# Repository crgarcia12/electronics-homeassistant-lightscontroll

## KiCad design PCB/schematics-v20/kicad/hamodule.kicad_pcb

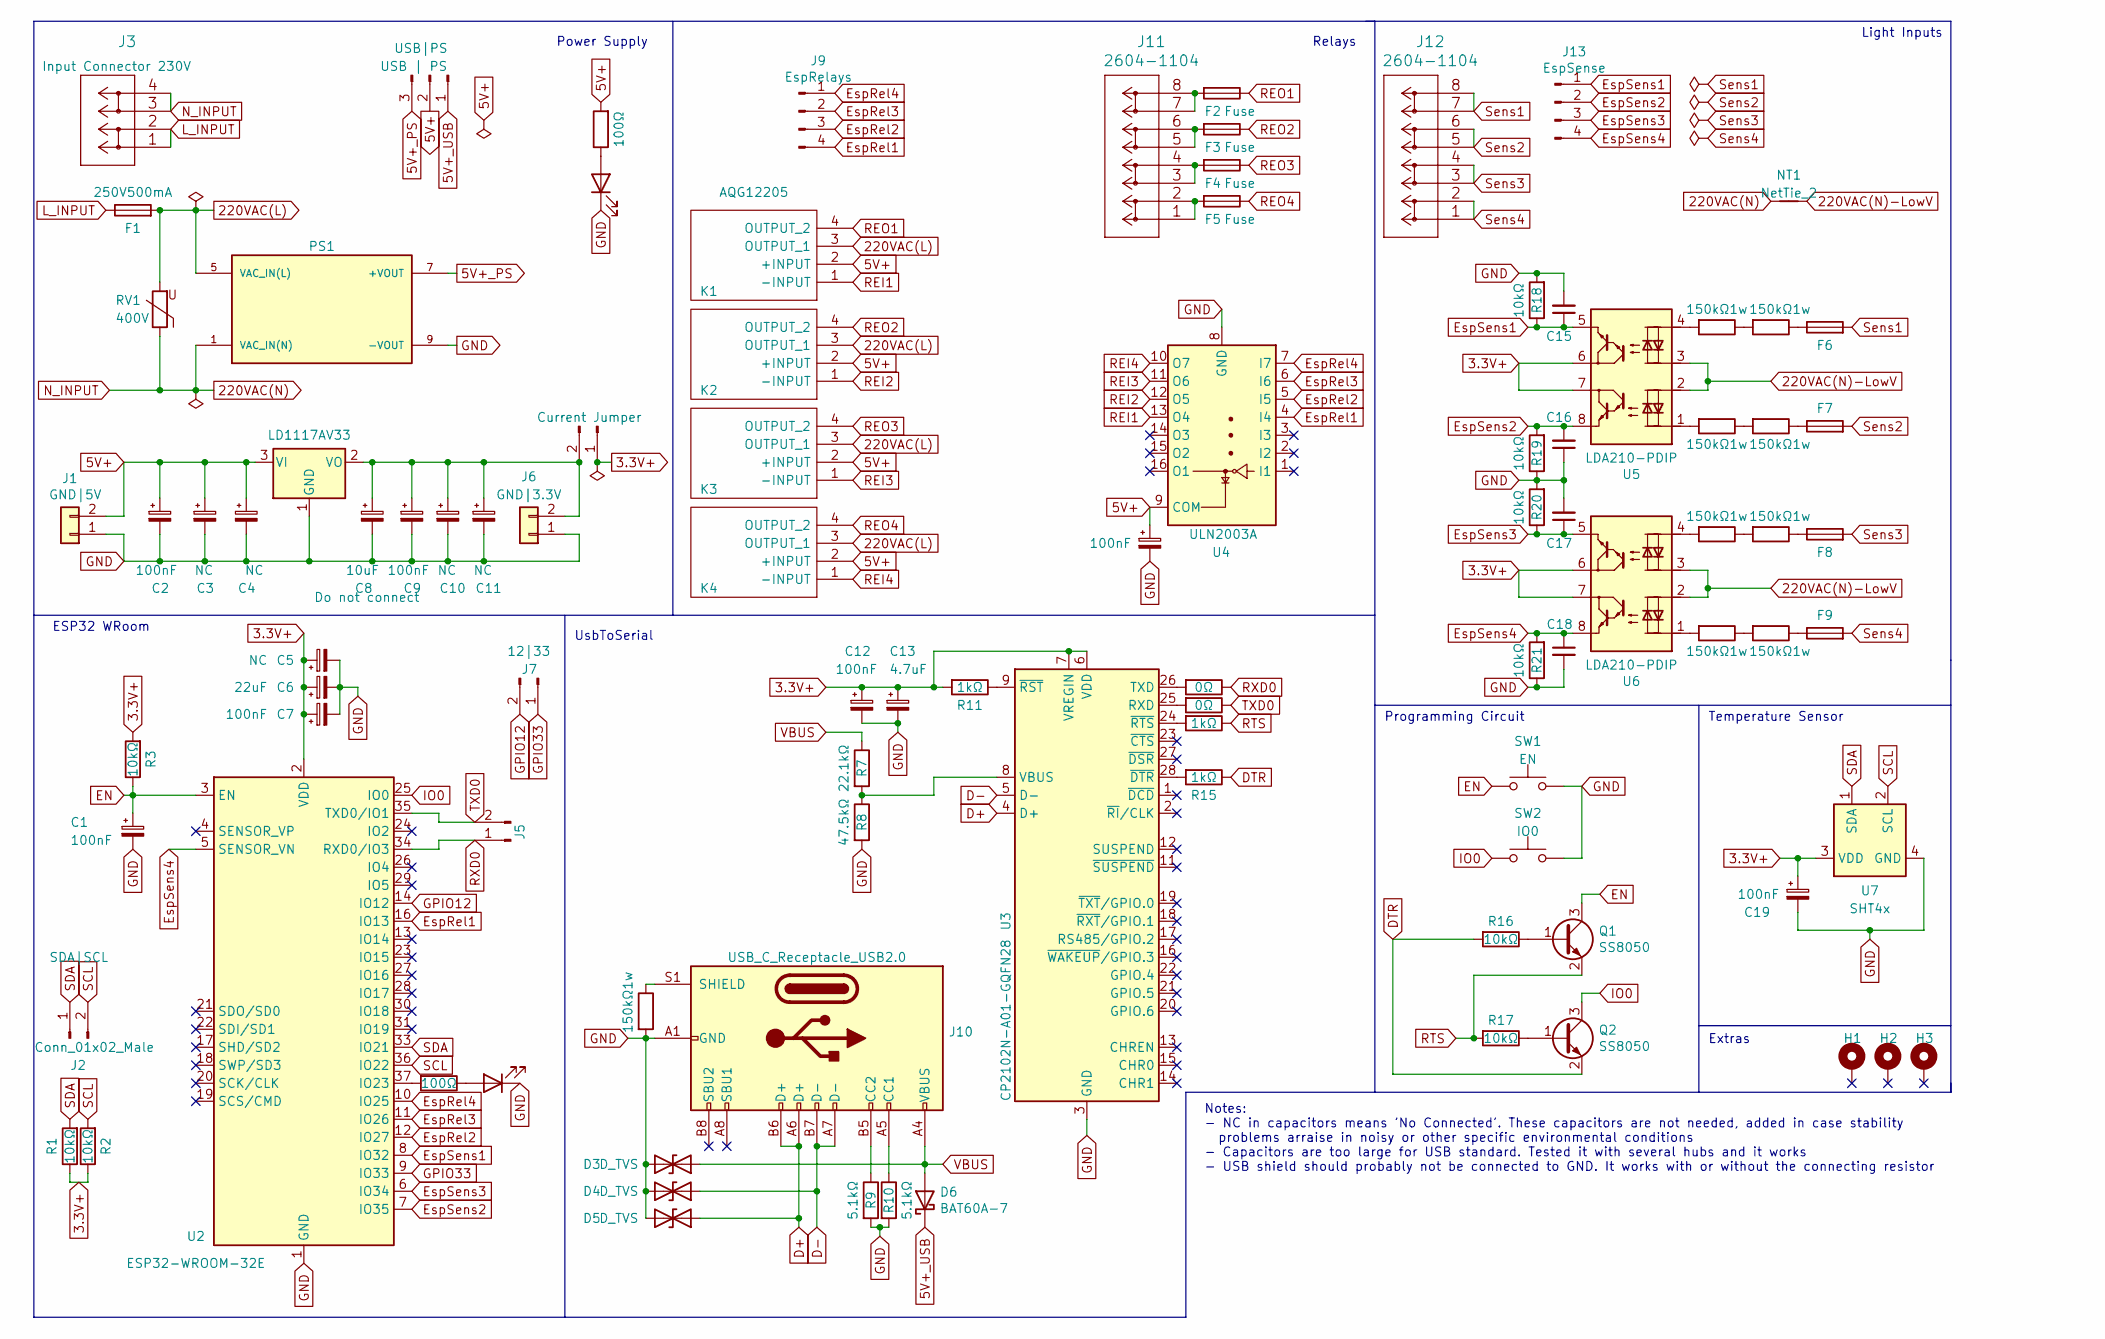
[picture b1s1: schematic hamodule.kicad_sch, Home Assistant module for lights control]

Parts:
C1, C2, C7, C9, C12, C14, C19: 100nF; C_0603_1608Metric_Pad1.08x0.95mm_HandSolder; JLCPCB C14663
C3, C4, C10, C11: NC; C_0805_2012Metric_Pad1.18x1.45mm_HandSolder
C5: NC; C_0603_1608Metric_Pad1.08x0.95mm_HandSolder
C6, C15, C16, C17, C18: 22uF; C_0603_1608Metric_Pad1.08x0.95mm_HandSolder; JLCPCB C59461
C8: 10uF; CP_Radial_D6.3mm_P2.50mm
C13: 4.7uF; C_0603_1608Metric_Pad1.08x0.95mm_HandSolder; JLCPCB C19666
D1, D2: LED; LED_0805_2012Metric_Pad1.15x1.40mm_HandSolder; JLCPCB C2297
D3, D4, D5: D_TVS; D_SOD-523; JLCPCB C383211
D6: BAT60A-7; D_SOD-323; JLCPCB C124187
F1: 250V500mA; Fuseholder_TR5_Littelfuse_No560_No460
F2, F3, F4, F5, F6, F7, F8, F9: Fuse; FUSE_RST-1-BULK
H1, H2, H3: MountingHole_Pad; MountingHole_3.2mm_M3_ISO14580_Pad
J1: GND|5V; JST_XH_B2B-XH-A_1x02_P2.50mm_Vertical
J2, J5, J7: Conn_01x02_Male; PinHeader_1x02_P2.54mm_Vertical
J3: 2604-1102; big_pads_2604-1102
J4: USB | PS; PinHeader_1x03_P2.54mm_Vertical
J6: GND|3.3V; JST_XH_B2B-XH-A_1x02_P2.50mm_Vertical
J8: Current Jumper; PinHeader_1x02_P2.54mm_Vertical
J9: EspRelays; PinSocket_1x04_P2.54mm_Vertical
J10: USB_C_Receptacle_USB2.0; USB_C_Receptacle_HRO_TYPE-C-31-M-12; JLCPCB C167321
J11, J12: 2604-1104; big_pads_2604-1104
J13: EspSense; PinSocket_1x04_P2.54mm_Vertical
K1, K2, K3, K4: AQG12205; Manufacturer_Part_Number AQG12205; Mouser Part Number 769-AQG12205
NT1: NetTie_2; NetTie-2_SMD_Pad2.0mm
PS1: RAC05-05SK/277; 277; PARTREV N/A
Q1, Q2: SS8050; SOT-23; JLCPCB C177739
R1, R2, R3, R16, R17, R18, R19, R20, R21: 10kΩ; R_0603_1608Metric_Pad0.98x0.95mm_HandSolder; JLCPCB C25804
R4, R5: 100Ω; R_0805_2012Metric_Pad1.20x1.40mm_HandSolder; JLCPCB C17408
R6, R22, R23, R24, R25, R26, R27, R28, R29: 150kΩ1w; R_2512_6332Metric_Pad1.40x3.35mm_HandSolder; JLCPCB C25719
R7: 22.1kΩ; R_0603_1608Metric_Pad0.98x0.95mm_HandSolder; JLCPCB C25961
R8: 47.5kΩ; R_0603_1608Metric_Pad0.98x0.95mm_HandSolder; JLCPCB C23061
R9, R10: 5.1kΩ; R_0603_1608Metric_Pad0.98x0.95mm_HandSolder; JLCPCB C23186
R11, R15: 1kΩ; R_0603_1608Metric_Pad0.98x0.95mm_HandSolder; JLCPCB C25585
R12, R13: 0Ω; R_0805_2012Metric_Pad1.20x1.40mm_HandSolder; JLCPCB C17477
R14: 1kΩ; R_1206_3216Metric_Pad1.30x1.75mm_HandSolder; JLCPCB C4410
RV1: 400V; RV_Disc_D12mm_W4.2mm_P7.5mm
SW1, SW2: Switch; SW_SPST_SKQG_WithStem; JLCPCB C318884
U1: LD1117AV33; TO-220-3_Vertical
U2: ESP32-WROOM-32E; ESP32-WROOM-32; JLCPCB C701343
U3: CP2102N-A01-GQFN28; QFN-28-1EP_5x5mm_P0.5mm_EP3.35x3.35mm; JLCPCB C964632
U4: ULN2003A; SOIC-16_3.9x9.9mm_P1.27mm; JLCPCB C7512
U5, U6: LDA210-PDIP; DIP-8_W7.62mm_Socket_LongPads
U7: SHT4x; XDCR_SHT40-AD1B-R2; JLCPCB C2909890

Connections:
3.3V+: C5.1, C6.1, C7.1, C12.1, C13.1, C19.1, J8.1, R1.1, R2.1, R3.2, R11.2, U2.2 (VDD), U3.6 (VDD), U3.7 (VREGIN), U5.6, U5.7, U6.6, U6.7, U7.3 (VDD)
5V+: C2.1, C3.1, C4.1, C14.1, J1.2, J4.2, K1.2 (+INPUT), K2.2 (+INPUT), K3.2 (+INPUT), K4.2 (+INPUT), R5.2, U1.3 (VI), U4.9 (COM)
5V+_PS: J4.3, PS1.7 (+VOUT)
5V+_USB: D6.1 (K), J4.1
220VAC(L): F1.2, K1.3 (OUTPUT_1), K2.3 (OUTPUT_1), K3.3 (OUTPUT_1), K4.3 (OUTPUT_1), PS1.5 (VAC_IN(L)), RV1.2
220VAC(N): J3.3, J3.4, NT1.1, PS1.1 (VAC_IN(N)), RV1.1
220VAC(N)-LowV: NT1.2, U5.2, U5.3, U6.2, U6.3
D+: D5.1 (A1), J10.A6 (D+), J10.B6 (D+), U3.4 (D+)
D-: D4.1 (A1), J10.A7 (D-), J10.B7 (D-), U3.5 (D-)
DTR: Q2.2 (E), R15.1, R16.2
EN: C1.1, Q1.3 (C), R3.1, SW1.1, U2.3 (EN)
EspRel1: J9.4, U2.16 (IO13), U4.4 (I4)
EspRel2: J9.3, U2.12 (IO27), U4.5 (I5)
EspRel3: J9.2, U2.11 (IO26), U4.6 (I6)
EspRel4: J9.1, U2.10 (IO25), U4.7 (I7)
EspSens1: C15.1, J13.1, R18.1, U2.8 (IO32), U5.5
EspSens2: C16.2, J13.2, R19.2, U2.7 (IO35), U5.8
EspSens3: C17.1, J13.3, R20.1, U2.6 (IO34), U6.5
EspSens4: C18.1, J13.4, R21.2, U2.5 (SENSOR_VN), U6.8
GND: C1.2, C2.2, C3.2, C4.2, C5.2, C6.2, C7.2, C8.2, C9.2, C10.2, C11.2, C12.2, C13.2, C14.2, C15.2, C16.1, C17.2, C18.2, C19.2, D1.1 (K), D2.1 (K), D3.2 (A2), D4.2 (A2), D5.2 (A2), J1.1, J6.1, J10.A1 (GND), J10.A12 (GND), J10.B1 (GND), J10.B12 (GND), PS1.9 (-VOUT), R6.2, R8.2, R9.2, R10.2, R18.2, R19.1, R20.2, R21.1, SW1.2, SW2.2, U1.1 (GND), U2.1 (GND), U2.15 (GND), U2.38 (GND), U2.39 (GND), U3.3 (GND), U3.29 (GND), U4.8 (GND), U7.4 (GND)
GPIO12: J7.2, U2.14 (IO12)
GPIO33: J7.1, U2.9 (IO33)
IO0: Q2.3 (C), SW2.1, U2.25 (IO0)
L_INPUT: F1.1, J3.1, J3.2
unnamed: C8.1, C9.1, C10.1, C11.1, J6.2, J8.2, U1.2 (VO)
unnamed: D1.2 (A), R4.1
unnamed: D2.2 (A), R5.1
unnamed: F6.1, R26.1
unnamed: F7.1, R27.1
unnamed: F8.1, R28.1
unnamed: F9.1, R29.1
unnamed: J10.A5 (CC1), R10.1
unnamed: J10.B5 (CC2), R9.1
unnamed: J10.S1 (SHIELD), R6.1
unnamed: F5.2, J11.1, J11.2
unnamed: F4.2, J11.3, J11.4
unnamed: F3.2, J11.5, J11.6
unnamed: F2.2, J11.7, J11.8
unnamed: Q1.1 (B), R16.1
unnamed: Q2.1 (B), R17.1
unnamed: R4.2, U2.37 (IO23)
unnamed: R7.2, R8.1, U3.8 (VBUS)
unnamed: R11.1, U3.9 (~RST)
unnamed: R12.2, U3.26 (TXD)
unnamed: R13.2, U3.25 (RXD)
unnamed: R14.2, U3.24 (~RTS)
unnamed: R15.2, U3.28 (~DTR)
unnamed: R22.1, R26.2
unnamed: R22.2, U5.4
unnamed: R23.1, R27.2
unnamed: R23.2, U5.1
unnamed: R24.1, R28.2
unnamed: R24.2, U6.4
unnamed: R25.1, R29.2
unnamed: R25.2, U6.1
REI1: K1.1 (-INPUT), U4.13 (O4)
REI2: K2.1 (-INPUT), U4.12 (O5)
REI3: K3.1 (-INPUT), U4.11 (O6)
REI4: K4.1 (-INPUT), U4.10 (O7)
REO1: F2.1, K1.4 (OUTPUT_2)
REO2: F3.1, K2.4 (OUTPUT_2)
REO3: F4.1, K3.4 (OUTPUT_2)
REO4: F5.1, K4.4 (OUTPUT_2)
RTS: Q1.2 (E), R14.1, R17.2
RXD0: J5.1, R12.1, U2.34 (RXD0/IO3)
SCL: J2.2, R2.2, U2.36 (IO22), U7.2 (SCL)
SDA: J2.1, R1.2, U2.33 (IO21), U7.1 (SDA)
Sens1: F6.2, J12.7, J12.8
Sens2: F7.2, J12.5, J12.6
Sens3: F8.2, J12.3, J12.4
Sens4: F9.2, J12.1, J12.2
TXD0: J5.2, R13.1, U2.35 (TXD0/IO1)
VBUS: D3.1 (A1), D6.2 (A), J10.A4 (VBUS), J10.A9 (VBUS), J10.B4 (VBUS), J10.B9 (VBUS), R7.1

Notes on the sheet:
Programming Circuit
UsbToSerial
Relays
Temperature Sensor
Power Supply
Extras
ESP32 WRoom
Notes: - NC in capacitors means 'No Connected'. These capacitors are not needed, added in case stability problems arraise in noisy or other specific environmental conditions - Capacitors are too large for USB standard. Tested it with several hubs and it works - USB shield should probably not be con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
Light Inputs

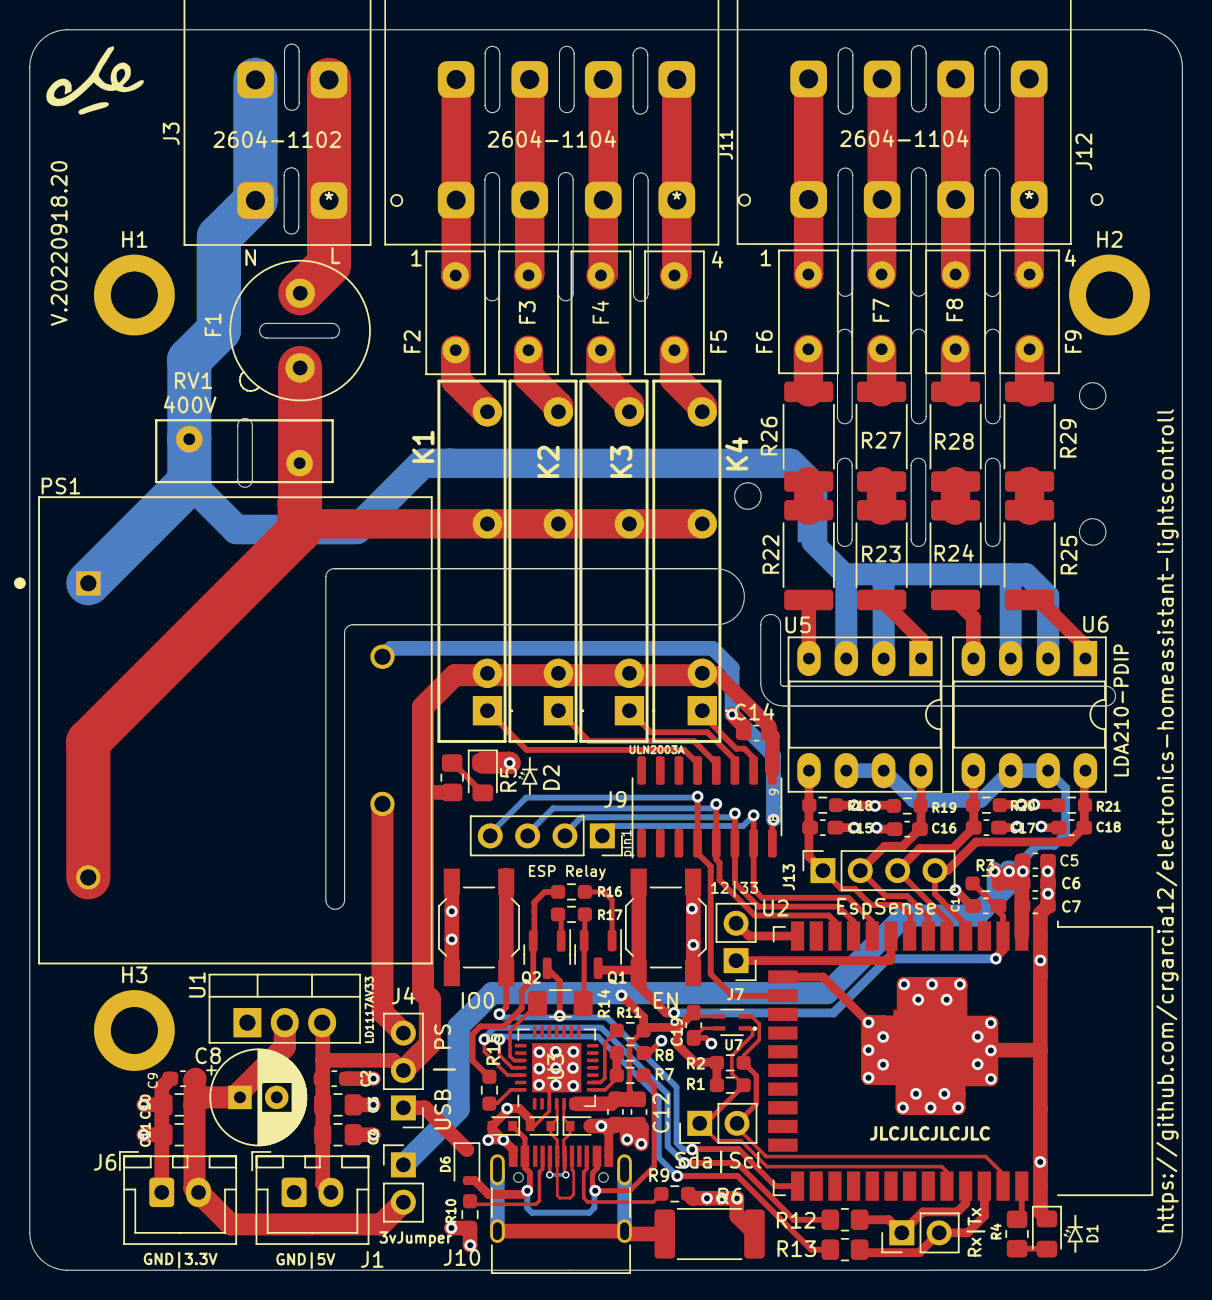
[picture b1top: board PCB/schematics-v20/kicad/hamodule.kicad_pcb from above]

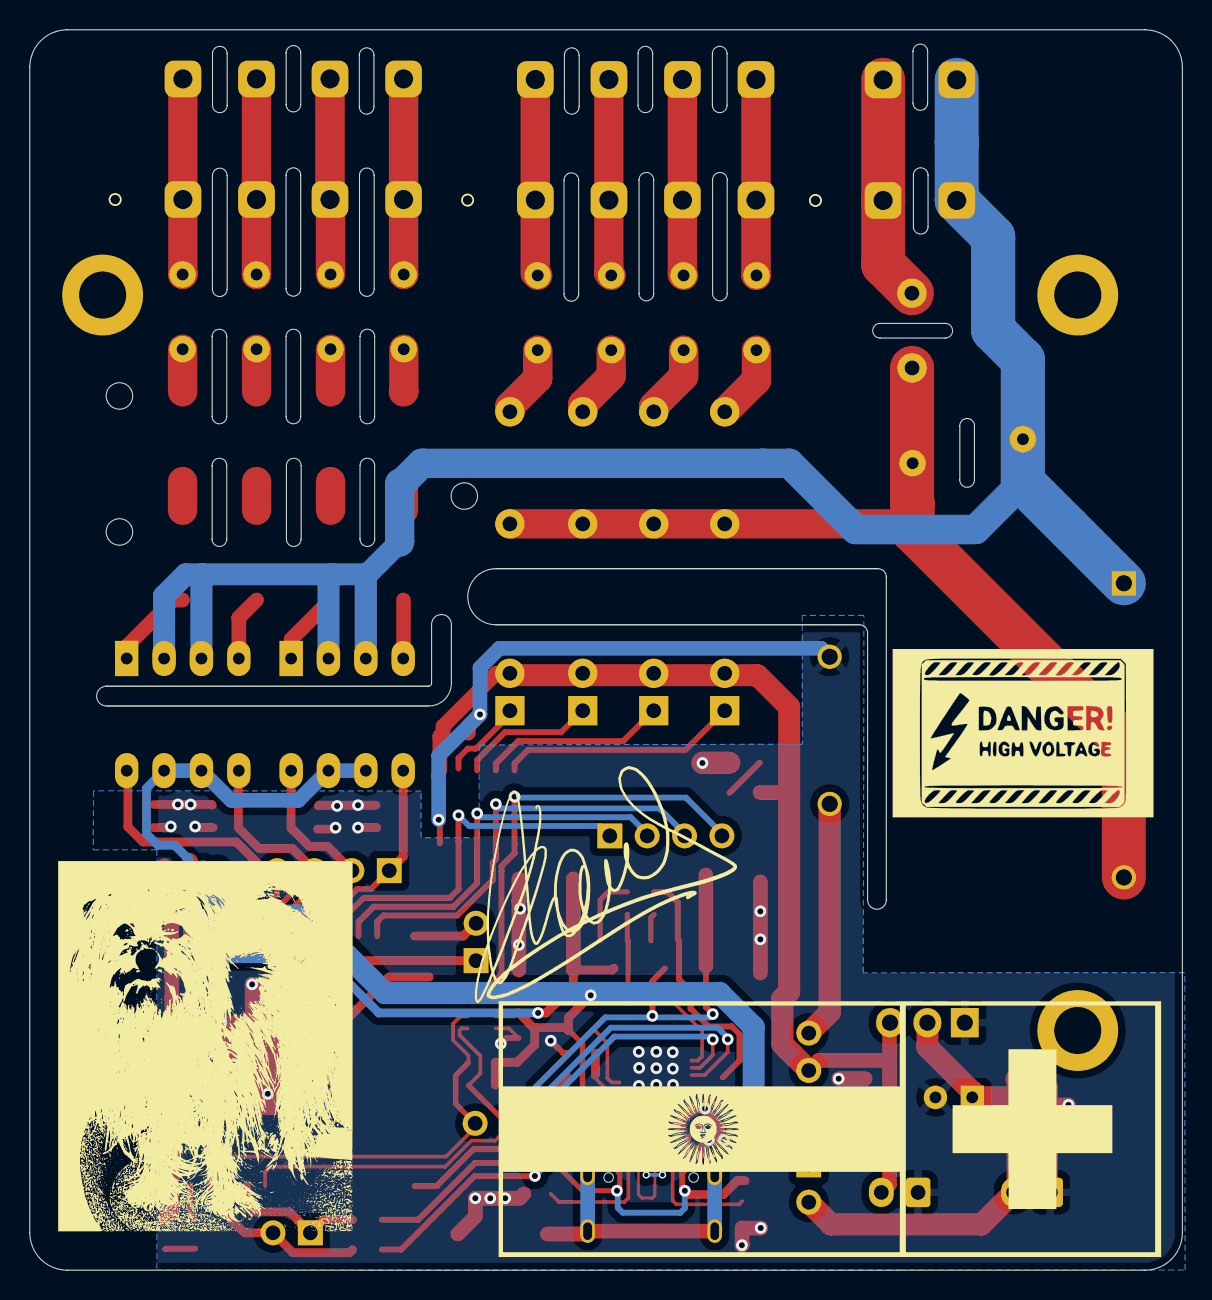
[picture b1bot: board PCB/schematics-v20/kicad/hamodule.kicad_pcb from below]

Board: 2 copper layers, 78.4 x 84.3 mm, 104 parts (5 on the bottom side), 73 nets.

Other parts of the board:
G1: LOGO; che
G2, G4: LOGO; led_6000dpi
G3: LOGO; danger1_negative
G5: LOGO; depsi
G6: LOGO; flags
G7: LOGO; paula

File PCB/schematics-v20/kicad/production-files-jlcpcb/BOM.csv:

Comment,Designator,Footprint,LCSC Part #
100nF Polarized capacitor  small symbol,"C1,C2,C7,C9,C12,C14,C19",Capacitor_SMD,C14663
NC Polarized capacitor  small symbol,"C3,C4,C10,C11",Capacitor_SMD,
NC Polarized capacitor  small symbol,C5,Capacitor_SMD,
22uF Unpolarized capacitor  small symbol,"C6,C15,C16,C17,C18",Capacitor_SMD,C59461
10uF Polarized capacitor  small symbol,C8,Capacitor_THT,
4.7uF Polarized capacitor  small symbol,C13,Capacitor_SMD,C19666
LED Light emitting diode,"D1,D2",LED_SMD,C2297
D_TVS Bidirectional transient-voltage-suppression diode,"D3,D4,D5",Diode_SMD,C383211
BAT60A-7 10V 3A High Current Recitifier Schottky Diode  SOD-323,D6,Diode_SMD,C124187
250V500mA Fuse,F1,Fuse,
Fuse Fuse,"F2,F3,F4,F5,F6,F7,F8,F9",RST-80-AMMO,
MountingHole_Pad Mounting Hole with connection,"H1,H2,H3",MountingHole,
GND|5V Generic connector  single row  01x02  script generated (k,J1,Connector_JST,
Conn_01x02_Male Generic connector  single row  01x02  script gen,"J2,J5,J7",Connector_PinHeader_2.54mm,
2604-1102 ,J3,wago-2604-1102,
USB | PS Generic connector  single row  01x03  script generated ,J4,Connector_PinHeader_2.54mm,
GND|3.3V Generic connector  single row  01x02  script generated ,J6,Connector_JST,
Current Jumper Generic connector  single row  01x02  script gene,J8,Connector_PinHeader_2.54mm,
EspRelays Generic connector  single row  01x04  script generated,J9,Connector_PinSocket_2.54mm,
USB_C_Receptacle_USB2.0 USB 2.0-only Type-C Receptacle connector,J10,Connector_USB,C167321
2604-1104 ,"J11,J12",wago-2604-1104,
EspSense Generic connector  single row  01x04  script generated ,J13,Connector_PinSocket_2.54mm,
AQG12205 Solid State Relays - PCB Mount 1A 5V Random Non-Zero Cr,"K1,K2,K3,K4",AQG12205,
NetTie_2 Net tie  2 pins,NT1,NetTie,
RAC05-05SK/277 ,PS1,rac05-05sk,
SS8050 NPN transistor  base/emitter/collector,"Q1,Q2",Package_TO_SOT_SMD,C177739
10k Resistor,"R1,R2,R3,R16,R17,R18,R19,R20,R21",Resistor_SMD,C25804
100 Resistor,"R4,R5",Resistor_SMD,C17408
150k1w Resistor,"R6,R22,R23,R24,R25,R26,R27,R28,R29",Resistor_SMD,C25719
22.1k Resistor,R7,Resistor_SMD,C25961
47.5k Resistor,R8,Resistor_SMD,C23061
5.1k Resistor,"R9,R10",Resistor_SMD,C23186
1k Resistor,"R11,R15",Resistor_SMD,C25585
0 Resistor,"R12,R13",Resistor_SMD,C17477
1k Resistor,R14,Resistor_SMD,C4410
400V Voltage dependent resistor,RV1,Varistor,
Switch Push button switch  generic  two pins,"SW1,SW2",Button_Switch_SMD,C318884
LD1117AV33 800mA Fixed Low Drop Positive Voltage Regulator  Fixe,U1,Package_TO_SOT_THT,
ESP32-WROOM-32E RF Module  ESP32-D0WD SoC  Wi-Fi 802.11b/g/n  Bl,U2,RF_Module,C701343
CP2102N-A01-GQFN28 USB to UART master bridge  QFN-28,U3,Package_DFN_QFN,C964632
ULN2003A High Voltage  High Current Darlington Transistor Arrays,U4,Package_SO,C7512
LDA210-PDIP DC Darlington Optocoupler  Vce 35V  CTR 600%  SO-4,"U5,U6",Package_DIP,
SHT4x Temperature and humidity module,U7,sht40,C2909890

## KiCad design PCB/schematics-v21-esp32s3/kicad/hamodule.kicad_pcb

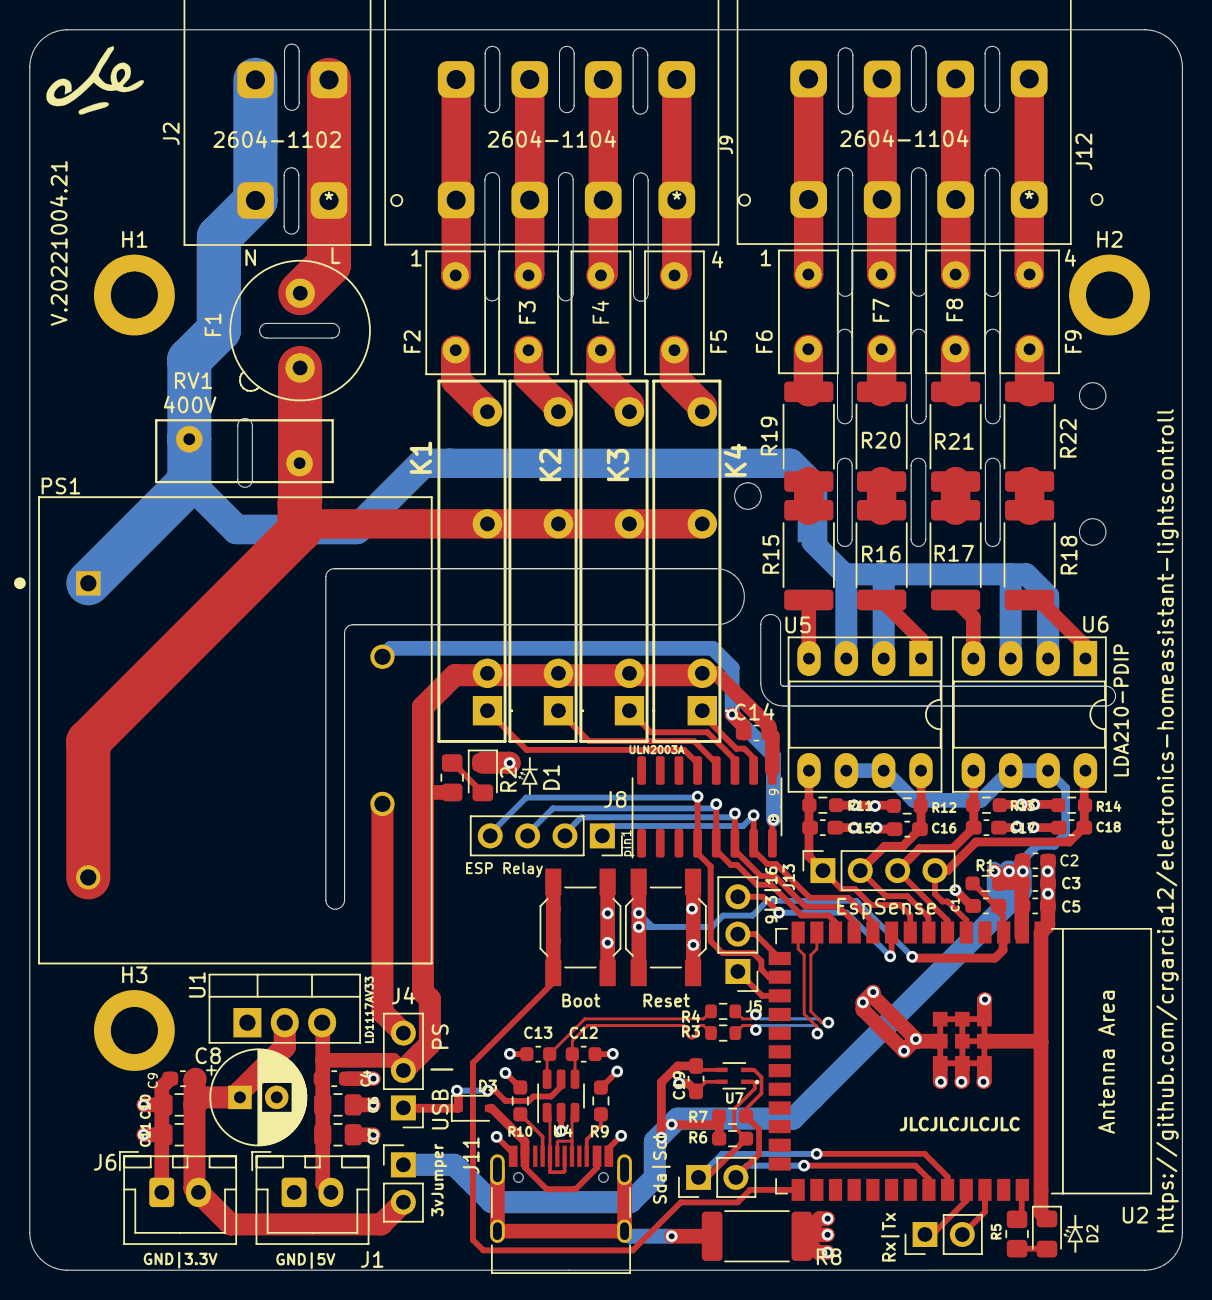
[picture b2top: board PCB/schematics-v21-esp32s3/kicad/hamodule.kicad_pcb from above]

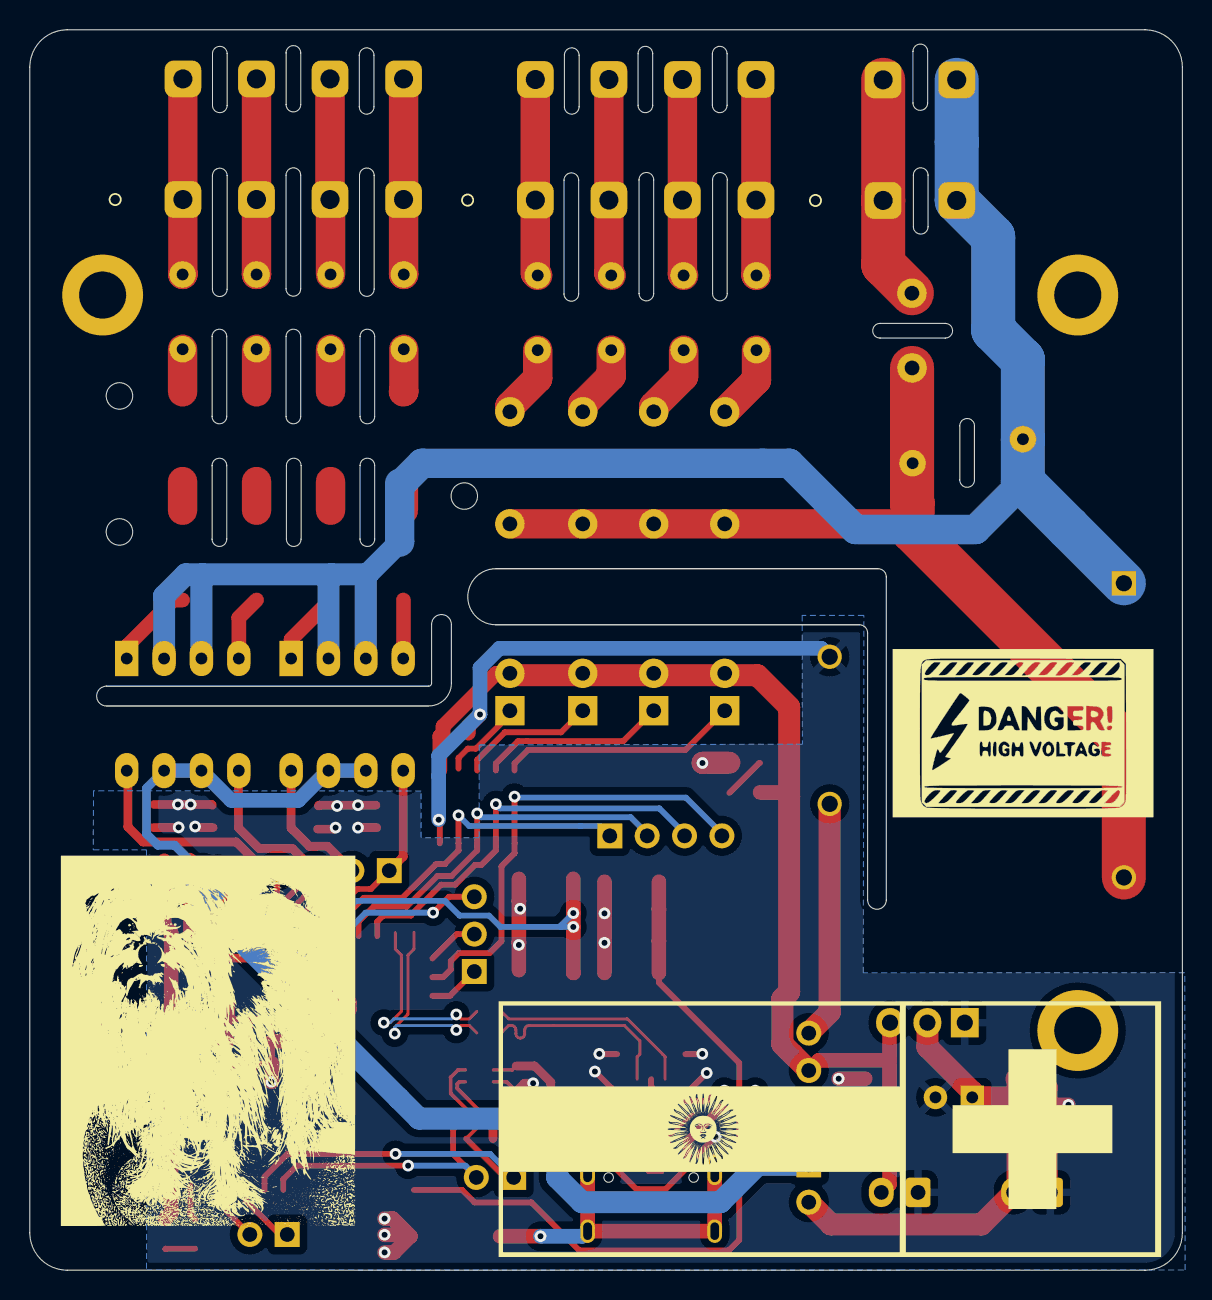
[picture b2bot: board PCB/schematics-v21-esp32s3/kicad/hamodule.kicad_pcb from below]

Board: 2 copper layers, 78.4 x 84.3 mm, 91 parts (4 on the bottom side), 68 nets.

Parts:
C1, C4, C5, C9, C14, C19: 100nF; C_0603_1608Metric_Pad1.08x0.95mm_HandSolder
C2: NC; C_0603_1608Metric_Pad1.08x0.95mm_HandSolder
C3, C15, C16, C17, C18: 22uF; C_0603_1608Metric_Pad1.08x0.95mm_HandSolder
C6, C7, C10, C11: NC; C_0805_2012Metric_Pad1.18x1.45mm_HandSolder
C8: 10uF; CP_Radial_D6.3mm_P2.50mm
C12, C13: 20p; C_0603_1608Metric
D1, D2: LED; LED_0805_2012Metric_Pad1.15x1.40mm_HandSolder
D3: BAT60A; D_SOD-323
F1: 250V500mA; Fuseholder_TR5_Littelfuse_No560_No460
F2, F3, F4, F5, F6, F7, F8, F9: Fuse; FUSE_RST-1-BULK
G1: LOGO; che
G2, G4: LOGO; led_6000dpi
G3: LOGO; danger1_negative
G5: LOGO; depsi
G6: LOGO; flags
H1, H2, H3: MountingHole_Pad; MountingHole_3.2mm_M3_ISO14580_Pad
J1: GND|5V; JST_XH_B2B-XH-A_1x02_P2.50mm_Vertical
J2: 2604-1102; big_pads_2604-1102
J3, J10: Conn_01x02_Male; PinHeader_1x02_P2.54mm_Vertical
J4: USB | PS; PinHeader_1x03_P2.54mm_Vertical
J5: Conn_01x02_Male; PinHeader_1x03_P2.54mm_Vertical
J6: GND|3.3V; JST_XH_B2B-XH-A_1x02_P2.50mm_Vertical
J7: Current Jumper; PinHeader_1x02_P2.54mm_Vertical
J8: EspRelays; PinSocket_1x04_P2.54mm_Vertical
J9, J12: 2604-1104; big_pads_2604-1104
J11: USB_C_Receptacle_USB2.0; USB_C_Receptacle_HRO_TYPE-C-31-M-12
J13: EspSense; PinSocket_1x04_P2.54mm_Vertical
K1, K2, K3, K4: AQG12205
NT1: NetTie_2; NetTie-2_SMD_Pad2.0mm
PS1: RAC05-05SK/277; 277
R1, R6, R7, R11, R12, R13, R14: 10kΩ; R_0603_1608Metric_Pad0.98x0.95mm_HandSolder
R2, R5: 100Ω; R_0805_2012Metric_Pad1.20x1.40mm_HandSolder
R3, R4: 22Ω; R_0603_1608Metric
R8, R15, R16, R17, R18, R19, R20, R21, R22: 150kΩ1w; R_2512_6332Metric_Pad1.40x3.35mm_HandSolder
R9, R10: 5.1kΩ; R_0603_1608Metric_Pad0.98x0.95mm_HandSolder
RV1: 400V; RV_Disc_D12mm_W4.2mm_P7.5mm
SW1, SW2: Switch; SW_SPST_SKQG_WithStem
U1: LD1117AV33; TO-220-3_Vertical
U2: ESP32-S3-WROOM-2
U3: ULN2003A; SOIC-16_3.9x9.9mm_P1.27mm
U4: USBLC6-2SC6; SOT-23-6
U5, U6: LDA210-PDIP; DIP-8_W7.62mm_Socket_LongPads
U7: SHT4x; XDCR_SHT40-AD1B-R2

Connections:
3.3V+: C2.1, C3.1, C5.1, C19.1, J7.1, R1.2, R6.1, R7.1, U2.2 (3V3), U5.6, U5.7, U6.6, U6.7, U7.3 (VDD)
5V+: C4.1, C6.1, C7.1, C14.1, J1.2, J4.2, K1.2 (+INPUT), K2.2 (+INPUT), K3.2 (+INPUT), K4.2 (+INPUT), R2.2, U1.3 (VI), U3.9 (COM)
5V+_PS: J4.3, PS1.7 (+VOUT)
220VAC(L): F1.2, K1.3 (OUTPUT_1), K2.3 (OUTPUT_1), K3.3 (OUTPUT_1), K4.3 (OUTPUT_1), PS1.5 (VAC_IN(L)), RV1.2
220VAC(N): J2.3, J2.4, NT1.1, PS1.1 (VAC_IN(N)), RV1.1
220VAC(N)-LowV: NT1.2, U5.2, U5.3, U6.2, U6.3
/ESP-D+: R3.1, U2.14 (GPIO20/U1CTS/ADC2_CH9/CLK_OUT1/USB_D+)
/ESP-D-: R4.1, U2.13 (GPIO19/U1RTS/ADC2_CH8/CLK_OUT2/USB_D-)
D+: C12.1, R3.2, U4.4 (I/O2)
D-: C13.2, R4.2, U4.6 (I/O1)
EN: C1.1, R1.1, SW1.1, U2.3 (EN)
EspRel1: J8.4, U2.16 (GPIO46), U3.4 (I4)
EspRel2: J8.3, U2.12 (GPIO8/TOUCH8/ADC1_CH7/SUBSPICS1), U3.5 (I5)
EspRel3: J8.2, U2.11 (GPIO18/U1RXD/ADC2_CH7/CLK_OUT3), U3.6 (I6)
EspRel4: J8.1, U2.10 (GPIO17/U1TXD/ADC2_CH6), U3.7 (I7)
EspSens1: C15.1, J13.1, R11.1, U2.8 (GPIO15/U0RTS/ADC2_CH4/XTAL_32K_P), U5.5
EspSens2: C16.2, J13.2, R12.2, U2.7 (GPIO7/TOUCH7/ADC1_CH6), U5.8
EspSens3: C17.1, J13.3, R13.1, U2.6 (GPIO6/TOUCH6/ADC1_CH5), U6.5
EspSens4: C18.1, J13.4, R14.2, U2.5 (GPIO5/TOUCH5/ADC1_CH4), U6.8
GND: C1.2, C2.2, C3.2, C4.2, C5.2, C6.2, C7.2, C8.2, C9.2, C10.2, C11.2, C12.2, C13.1, C14.2, C15.2, C16.1, C17.2, C18.2, C19.2, D1.1 (K), D2.1 (K), J1.1, J6.1, J11.A1 (GND), J11.A12 (GND), J11.B1 (GND), J11.B12 (GND), PS1.9 (-VOUT), R8.2, R9.2, R10.2, R11.2, R12.1, R13.2, R14.1, SW1.2, SW2.2, U1.1 (GND), U2.1 (GND), U2.40 (GND), U2.41 (GND), U3.8 (GND), U4.2 (GND), U7.4 (GND)
GPIO3: J5.2, U2.15 (GPIO3/TOUCH3/ADC1_CH2)
GPIO9: J5.1, U2.17 (GPIO9/TOUCH9/ADC1_CH8/FSPIHD/SUBSPIHD)
GPIO16: J5.3, U2.9 (GPIO16/U0CTS/ADC2_CH5/XTAL_32K_NH5)
IO0: SW2.1, U2.27 (GPIO0/BOOT)
LED-GPIO: R5.2, U2.39 (GPIO1/TOUCH1/ADC1_CH0)
L_INPUT: F1.1, J2.1, J2.2
unnamed: C8.1, C9.1, C10.1, C11.1, J6.2, J7.2, U1.2 (VO)
unnamed: D1.2 (A), R2.1
unnamed: D2.2 (A), R5.1
unnamed: D3.2 (A), J11.A4 (VBUS), J11.A9 (VBUS), J11.B4 (VBUS), J11.B9 (VBUS)
unnamed: F2.2, J9.7, J9.8
unnamed: F3.2, J9.5, J9.6
unnamed: F4.2, J9.3, J9.4
unnamed: F5.2, J9.1, J9.2
unnamed: F6.1, R19.1
unnamed: F7.1, R20.1
unnamed: F8.1, R21.1
unnamed: F9.1, R22.1
unnamed: J11.A5 (CC1), R10.1
unnamed: J11.B5 (CC2), R9.1
unnamed: J11.S1 (SHIELD), R8.1
unnamed: R15.1, R19.2
unnamed: R15.2, U5.4
unnamed: R16.1, R20.2
unnamed: R16.2, U5.1
unnamed: R17.1, R21.2
unnamed: R17.2, U6.4
unnamed: R18.1, R22.2
unnamed: R18.2, U6.1
REI1: K1.1 (-INPUT), U3.13 (O4)
REI2: K2.1 (-INPUT), U3.12 (O5)
REI3: K3.1 (-INPUT), U3.11 (O6)
REI4: K4.1 (-INPUT), U3.10 (O7)
REO1: F2.1, K1.4 (OUTPUT_2)
REO2: F3.1, K2.4 (OUTPUT_2)
REO3: F4.1, K3.4 (OUTPUT_2)
REO4: F5.1, K4.4 (OUTPUT_2)
RXD0: J10.1, U2.36 (U0RXD/GPIO44/CLK_OUT2)
SCL: J3.2, R7.2, U2.34 (MTDI/GPIO41/CLK_OUT1), U7.2 (SCL)
SDA: J3.1, R6.2, U2.35 (MTMS/GPIO42), U7.1 (SDA)
Sens1: F6.2, J12.7, J12.8
Sens2: F7.2, J12.5, J12.6
Sens3: F8.2, J12.3, J12.4
Sens4: F9.2, J12.1, J12.2
TXD0: J10.2, U2.37 (U0TXD/GPIO43/CLK_OUT1)
USB-D+: J11.A6 (D+), J11.B6 (D+), U4.3 (I/O2)
USB-D-: J11.A7 (D-), J11.B7 (D-), U4.1 (I/O1)
VBUS: D3.1 (K), J4.1, U4.5 (VBUS)

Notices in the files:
parts and their libraries:
Copyright 2021 Accelerated Designs. All rights reserved.
